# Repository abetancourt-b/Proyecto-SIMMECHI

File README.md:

# Requisitos Python - VS Code:

En terminal instalar:

- pip install flask

# Requisitos Arduino IDE:

En Gestor de Bibliotecas instalar:

- Firebase ESP32 Client by: Mobizt

- Adafruit BMP280 Library by: Adafruit

- Adafruit Unified Sensor by: Adafruit

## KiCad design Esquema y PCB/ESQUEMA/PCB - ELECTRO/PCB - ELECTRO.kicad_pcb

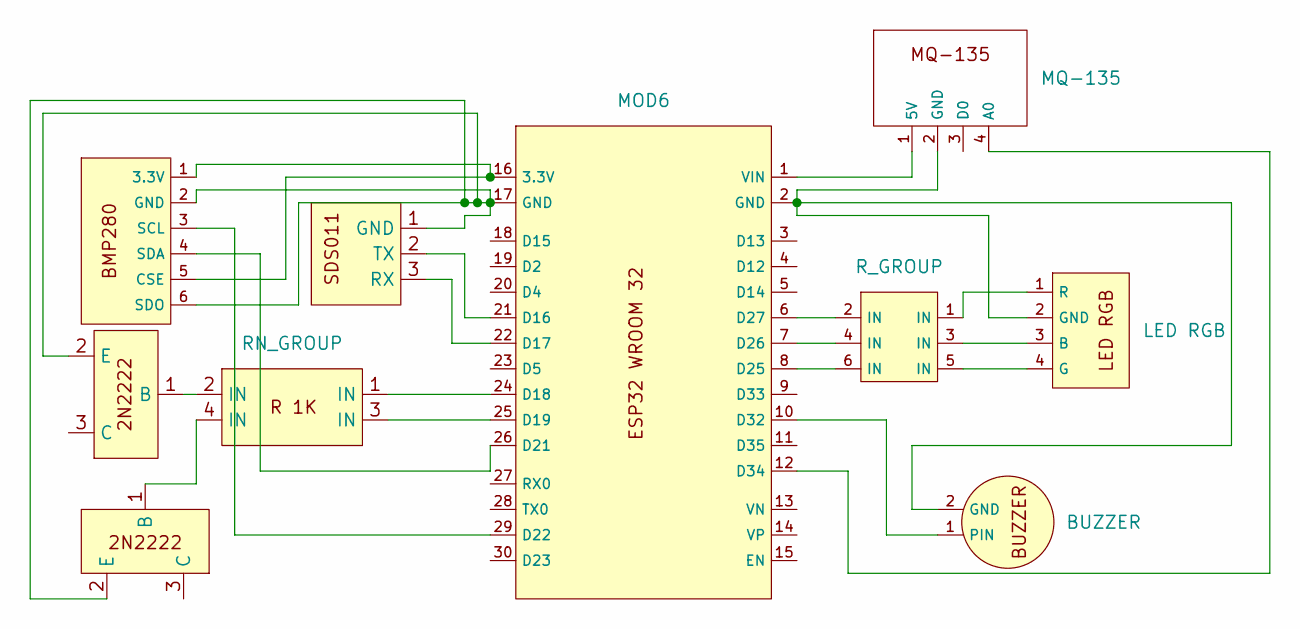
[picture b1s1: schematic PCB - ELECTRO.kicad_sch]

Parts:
MOD1: MQ-135
MOD2: BMP280
MOD3: SDS011
MOD4: LED RGB
MOD5: BUZZER
MOD6: MOD; ESP32 WROOM 32
U1, U3: 2N2222
U2: R_GROUP; GROUP_R
U4: RN_GROUP

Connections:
unnamed: MOD1.1 (5V), MOD6.1 (VIN)
unnamed: MOD1.4 (A0), MOD6.12 (D34)
unnamed: MOD1.2 (GND), MOD4.2 (GND), MOD5.2 (GND), MOD6.2 (GND)
unnamed: MOD2.1 (3.3V), MOD2.5 (CSE), MOD6.16 (3.3V)
unnamed: MOD2.2 (GND), MOD2.6 (SDO), MOD3.1 (GND), MOD6.17 (GND), U1.2 (E), U3.2 (E)
unnamed: MOD2.3 (SCL), MOD6.29 (D22)
unnamed: MOD2.4 (SDA), MOD6.26 (D21)
unnamed: MOD3.3 (RX), MOD6.22 (D17)
unnamed: MOD3.2 (TX), MOD6.21 (D16)
unnamed: MOD4.3 (B), U2.3 (IN)
unnamed: MOD4.4 (G), U2.5 (IN)
unnamed: MOD4.1 (R), U2.1 (IN)
unnamed: MOD5.1 (PIN), MOD6.10 (D32)
unnamed: MOD6.24 (D18), U4.1 (IN)
unnamed: MOD6.25 (D19), U4.3 (IN)
unnamed: MOD6.8 (D25), U2.6 (IN)
unnamed: MOD6.7 (D26), U2.4 (IN)
unnamed: MOD6.6 (D27), U2.2 (IN)
unnamed: U1.1 (B), U4.4 (IN)
unnamed: U3.1 (B), U4.2 (IN)

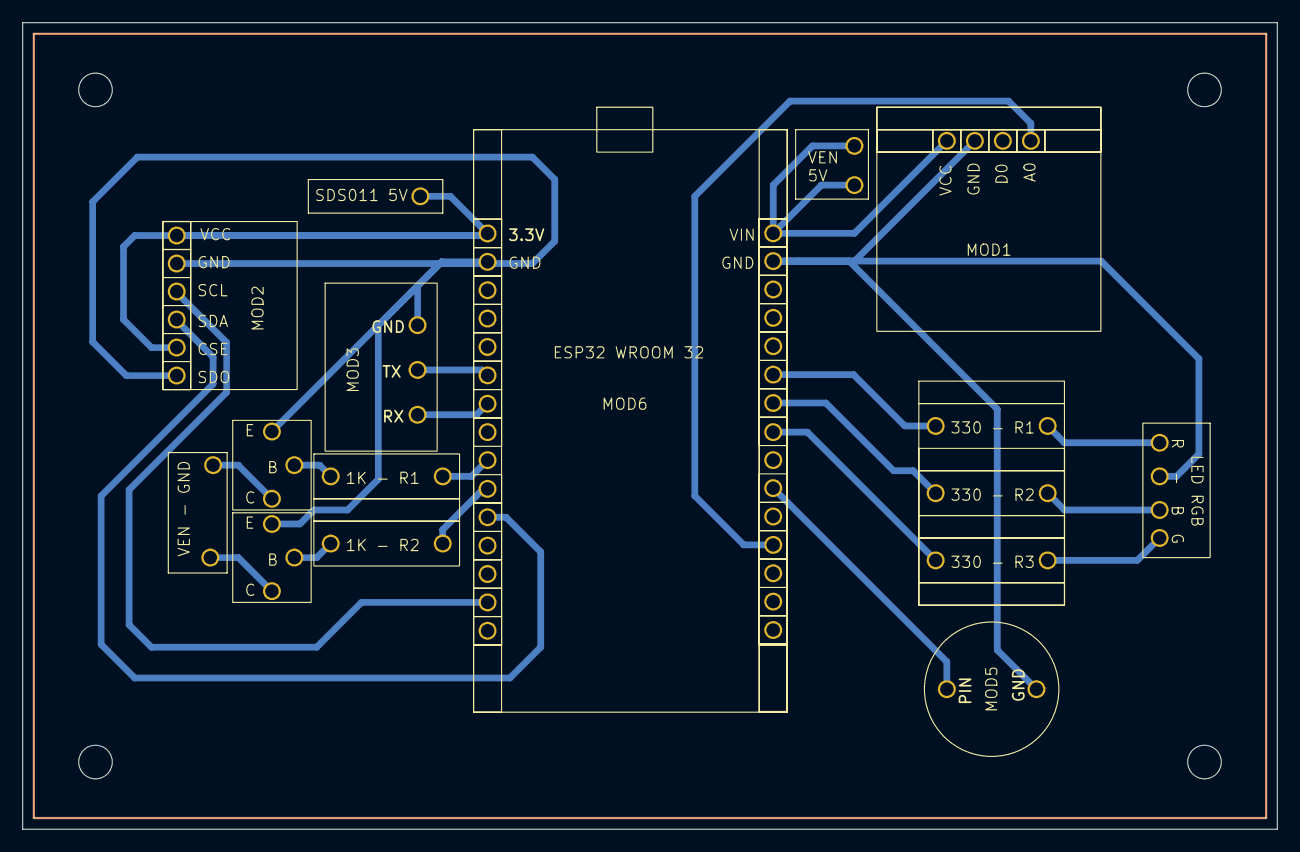
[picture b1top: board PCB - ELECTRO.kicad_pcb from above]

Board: 2 copper layers, 112.0 x 72.0 mm, 10 parts (0 on the bottom side), 20 nets.

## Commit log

2025-12-13 Fix formatting in README.md
2025-12-13 Revise Arduino IDE library installation instructions
    Updated installation instructions for Arduino IDE.
